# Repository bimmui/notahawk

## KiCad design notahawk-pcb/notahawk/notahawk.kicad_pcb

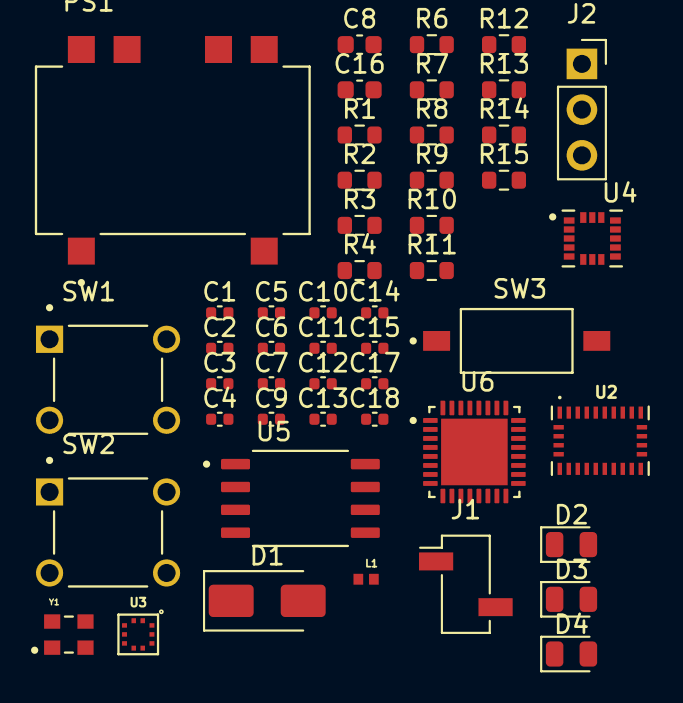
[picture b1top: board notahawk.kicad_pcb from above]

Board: 2 copper layers, 49 parts (0 on the bottom side), 33 nets, no tracks yet.

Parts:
C1, C2, C3, C4, C5, C6, C7, C9, C10, C11, C12, C13, C14, C15, C17, C18: 100 nF; C_0402_1005Metric
C8: 1000 nF; C_0603_1608Metric
C16: 4700 nF; C_0603_1608Metric
D1: SS14; D_SMA
D2: POWER LED; LED_0805_2012Metric
D3: BOOTLOADER LED; LED_0805_2012Metric
D4: STATUS LED; LED_0805_2012Metric
J1: Conn_01x02_Pin; PinSocket_1x02_P2.54mm_Vertical_SMD_Pin1Left
J2: USB-to-TTL cable; PinSocket_1x03_P2.54mm_Vertical
L1: 20 nH; INDC1005X55N
PS1: TSR_1-2433SM; CONV_TSR_1-2433SM
R1, R4, R6, R7, R8, R10, R11, R12, R13: 10k; R_0603_1608Metric
R2, R3, R9: 4.7k; R_0603_1608Metric
R14, R15: 1k; R_0603_1608Metric
SW1: Reset button; SW_TS02-66-50-BK-100-LCR-D
SW2: Bootloader button; SW_TS02-66-50-BK-100-LCR-D
SW3: SW_SPST; SW_DS04-254-2-01BK-SMT
U2: BNO085; IC_BNO085
U3: BMP581
U4: ADXL372BCCZ-RL7; PQFN50P322X300X114-16N
U5: W25Q128JVSIQ; SOIC127P790X216-8N
U6: ESP32-C3; QFN50P500X500X90-33N
Y1: ECS-TXO-2520-33-400-AN-TR; OSC_ECS-TXO-2520-33-400-AN-TR

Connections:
+3.3V: C2.1, C3.2, C4.2, C5.2, C7.2, C9.2, C11.2, C12.2, C13.2, C14.2, C15.2, C16.2, C17.2, D2.2 (A), PS1.5 (+VOUT), R1.2, R4.2, R6.2, R7.2, R8.2, R9.2, R10.2, R11.2, R12.2, R13.2, R14.1, U2.3 (VDD), U2.28 (VDDIO), U3.1 (VDDIO), U3.6 (CSB), U3.10 (VDD), U4.1 (VDDI/O), U5.8 (VCC), U6.2 (VDD3P3), U6.3 (VDD3P3), U6.11 (VDD3P3_RTC), U6.17 (VDD3P3_CPU), U6.18 (VDD_SPI), U6.31 (VDDA), U6.32 (VDDA), Y1.4 (VDD)
/ADXL372 CS: R9.1, U4.8 (~CS/SCL), U6.8 (GPIO3)
/ADXL372 INT: U4.11 (INT1), U6.25 (GPIO18/USB_D-)
/BNO085 RST: R13.1, U2.11 (~RST), U6.5 (GPIO1/XTAL_32K_N)
/ESP BOOT: D3.1 (K), R12.1, SW2.1, U6.15 (GPIO9)
/ESP ENABLE: C18.2, R11.1, SW1.1, U6.7 (CHIP_EN)
/ESP MISO: U4.7 (MISO), U5.2 (DO(IO1)), U6.23 (GPIO16/SPID)
/ESP MOSI: U4.6 (MOSI/SDA), U5.5 (DI(IO0)), U6.24 (GPIO17/SPIQ)
/ESP SCL: R3.2, U2.19 (H_SCL/SCK/RX), U3.2 (SCK/SCL)
/ESP SCLK: U4.4 (SCLK), U5.6 (CLK), U6.22 (GPIO15/SPICLK)
/ESP SDA: R2.2, U2.20 (H_SDA/H_MISO/TX), U3.4 (SDI/SDA)
/ESP STATUS: R15.1, U6.26 (GPIO19/USB_D+)
/ESP XTAL_P: L1.2, U6.30 (XTAL_P)
/VBUS: D1.2 (A), SW3.1 (A)
/W25Q128 CS: R8.1, U5.1 (/CS), U6.4 (GPIO0/XTAL_32K_P)
GND: C1.1, C2.2, C3.1, C4.1, C5.1, C6.1, C7.1, C8.1, C9.1, C10.1, C11.1, C12.1, C13.1, C14.1, C15.1, C16.1, C17.1, C18.1, D2.1 (K), D4.1 (K), J1.1, J2.1, PS1.7 (GND), PS1.9 (GND), SW1.2, SW2.2, U2.2 (GND), U2.5 (PS1), U2.6 (PS0/WAKE), U2.17 (SA0/H_MOSI), U2.25 (GNDIO), U3.3 (GND), U3.5 (SDO/ADR), U3.8 (GND), U3.9 (GND), U4.12 (GND), U4.13 (GND), U4.16 (GND), U6.33 (GND), Y1.2 (GND)
unnamed: D1.1 (K), PS1.1 (+VIN)
unnamed: D3.2 (A), R14.2
unnamed: D4.2 (A), R15.2
unnamed: J1.2, SW3.2 (B)
unnamed: J2.2, U6.28 (GPIO21/U0TXD)
unnamed: J2.3, U6.27 (GPIO20/U0RXD)
unnamed: C1.2, U2.9 (CAP)
unnamed: R4.1, U2.10 (CLKSEL0)
unnamed: R1.1, U2.4 (~BOOT)
unnamed: C6.2, C8.2, U4.14 (VS)
unnamed: C10.2, U5.4 (GND)
unnamed: R7.1, U5.7 (/HOLD/RESET(IO3))
unnamed: R6.1, U5.3 (/WP(IO2))
unnamed: R2.1, U6.14 (GPIO8)
unnamed: R3.1, U6.16 (GPIO10)
unnamed: L1.1, Y1.3 (OUTPUT)
unnamed: R10.1, Y1.1 (TRI-STATE)

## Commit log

2025-11-27 Initial commit of project files
2025-11-29 started notahawk schematic
    TODO:
    - add oscillator crystal
    - add pins to upload code onto esp
    - add QOL features to help debug
2025-11-29 developed sims a bit more
    made progress on rocketpy sim, refer to notes (paper notes) on airfoil shit
2025-11-30 almost done w schematic
    knocked off stuff from todo and then some. did circuit to handle boot/download/power modes
    TODO:
    - add QOL features to help debug board
2025-12-01 finished schematic
2025-12-01 tiny changes
2025-12-02 fixed erc errors on schematic
2025-12-03 mo footprints
2025-12-05 footprints assigned, finished schematic for good, starting pcb
